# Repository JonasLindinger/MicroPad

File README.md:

# MicroPad — Wi-Fi MQTT Controller for Home Assistant

> AI-assisted development — firmware, HA automation, config generator and docs were created with AI (LLM) help, reviewed and tested by the author. Provided as-is, without warranty; verify on your own hardware, don't use for safety-critical applications.

MicroPad is a small ESP32-S3 desk controller with a 2.9" e-paper display, a 3×4
key matrix, and a rotary encoder. It talks to Home Assistant over MQTT and shows
clickable pages of your devices, media, scripts, scenes, and numbers. This
repository contains the firmware, the Home Assistant automation generator, the
web configurator, and the deployment/service assets.

## Safety

- **Not safety-critical.** This project is a convenience input device. Do not use
  it, or rely on it, for safety-critical applications (life-safety, medical,
  security, or anything where a missed or delayed press could cause harm). The
  room always retains the Home Assistant UI as the authoritative control surface.
- **Verify on your own hardware.** Firmware behaviour is validated by the compile
  matrix and host/static suites on this build machine, but no physical MicroPad
  hardware was available during development. Every hardware acceptance row is
  intentionally unchecked until an operator executes it on real hardware. Never
  assume a feature works on your specific board; test it.
- **Neutral placeholders only.** Source contains no real credentials. The broker
  host placeholder is `192.168.0.100`, the service user is `micropad`, and the
  placeholder password is `replace-me`. Real Wi-Fi/MQTT credentials are entered
  only through the on-device setup portal and stored in NVS.
- **Charge-only chargers.** A charge-only wall charger (no enumerated USB host)
  intentionally follows normal battery sleep behaviour: no power icon is drawn
  and light sleep is allowed. Only an enumerated USB data host keeps the device
  fully awake. See `docs/hardware-acceptance.md`.

## Reproducibility

The Python dependency graph is locked: `uv.lock` is the resolved source of
truth, and `requirements-lock.txt` is its content-hash materialization (every
wheel pinned with `sha256`, regenerated with `uv export --frozen`). The build
backend is pinned exactly (`setuptools==84.0.0`). This freezes dependency
*versions and content*; it does **not** claim byte-identical builds, because
pip/setuptools release artifacts can still vary between environments. Generated
automation/payload artifacts are deterministic per configuration (see below).

## Quick start

Create a virtualenv and install the package and dev tools (Ubuntu/Debian shown):

```bash
python3 -m venv .venv
.venv/bin/pip install --requirement requirements-dev.txt
```

For a content-hash-pinned runtime install (every transitive dependency locked in
`uv.lock` and materialized as `requirements-lock.txt` with `sha256` hashes)
instead use:

```bash
.venv/bin/pip install --requirement requirements-lock.txt
```

Run the configurator locally for development (Flask dev server):

```bash
.venv/bin/python -m flask --app micropad.wsgi:app run --host 127.0.0.1 --port 8080
```

Check it is healthy:

```bash
curl http://127.0.0.1:8080/healthz
# -> {"ok": true, "service": "micropad-configurator"}
```

For production, install the systemd service under `/opt/micropad/app` (root):

```bash
sudo ./scripts/setup.sh --enable-service
journalctl -u micropad.service -f
```

The on-device network setup and the build/flash workflow are described in
`docs/firmware.md`.

## Firmware

The firmware lives in `firmware/` (`MicroPad_HA_Controller.ino`,
`micropad_core.*`, and `protocol_contract.h`). It is built with Arduino CLI 1.5.1,
ESP32 core 3.3.11, GxEPD2 1.6.9, ArduinoJson 7.4.3, and PubSubClient 2.8.

```bash
./scripts/install-arduino-toolchain.sh        # pin the exact toolchain
./scripts/compile-firmware.sh --print-matrix  # list the three pinned FQBNs
./scripts/compile-firmware.sh                 # compile all matrix FQBNs
```

See `docs/firmware.md` for the pin map, build/flash commands, the setup portal,
and sleep behaviour.

## Home Assistant

A single MQTT automation (id `micropad_controller`) turns `micropad/event` and
`micropad/power` publications into device actions and re-publishes the
authoritative `micropad/pages/all`, `micropad/page/current`, and `micropad/keymap`
retained payloads. The automation and the retained initial payloads are generated
by `src/micropad/generator.py` and are byte-identical for the same configuration.

You can deliver the generated automation two ways:

- **API upload** — the configurator writes the automation directly to Home
  Assistant via its REST API and verifies the read-back, then publishes the
  retained MQTT payloads.
- **SSH upload** — the configurator uploads a YAML file to your Home Assistant
  host over SFTP/SSH with strict host-key checking and reloads, for setups where
  the REST API path is not available.

Both are covered in `docs/home-assistant.md`.

## Configurator

The Flask web configurator (`src/micropad/app.py`) validates your configuration,
lets you edit pages, key maps, and entity bindings in the browser, discovers
Home Assistant entities, and generates or uploads the automation.

- `GET /api/config` — current public configuration (credentials redacted).
- `POST /api/config` — validate and save a configuration.
- `POST /api/validate` — validate without saving.
- `POST /api/upload/api` — deploy via the Home Assistant REST API.
- `POST /api/upload/ssh` — deploy via SFTP/SSH.
- `GET /api/meta` — contract version, the fourteen key IDs, actions, item types,
  templates, and the default keymap.

See `docs/configurator.md` for the pages editor, key editor, entity discovery,
and validation rules, and `docs/deployment.md` for install/update/logs/uninstall.

---

Licensed under the [MIT License](LICENSE) (Copyright (c) 2026 Jonas Lindinger).
All content above is written in neutral English and uses only the placeholder
values described in the **Safety** section.

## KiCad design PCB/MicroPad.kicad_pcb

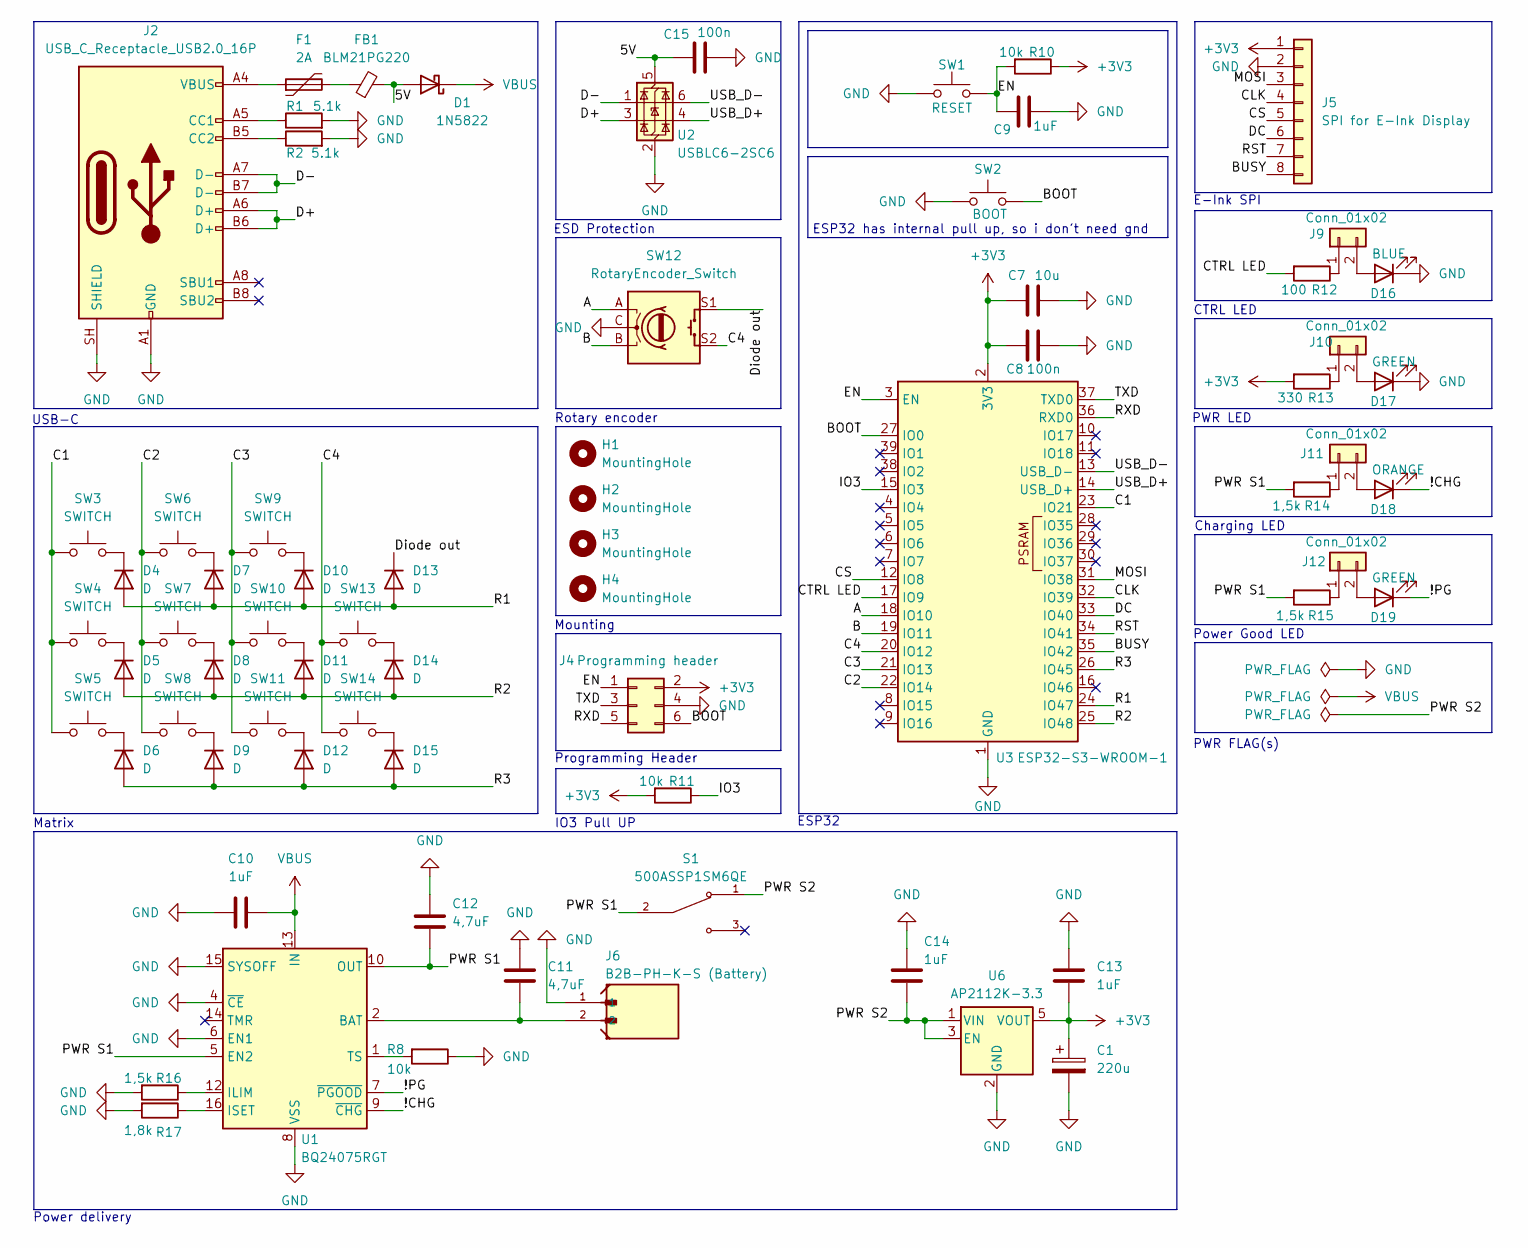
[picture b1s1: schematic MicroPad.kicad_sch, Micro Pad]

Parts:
C1: 220u; CP_Elec_6.3x7.7
C7: 10u; C_0805_2012Metric_Pad1.18x1.45mm_HandSolder
C8, C15: 100n; C_0805_2012Metric_Pad1.18x1.45mm_HandSolder
C9, C10, C13, C14: 1uF; C_0805_2012Metric_Pad1.18x1.45mm_HandSolder
C11, C12: 4,7uF; C_0805_2012Metric_Pad1.18x1.45mm_HandSolder
D1: 1N5822; D_DO-201AD_P15.24mm_Horizontal
D4, D5, D6, D7, D8, D9, D10, D11, D12, D13, D14, D15: D; D_SMA
D16: BLUE; LED_D3.0mm
D17, D19: GREEN; LED_D3.0mm
D18: ORANGE; LED_D3.0mm
F1: 2A; Fuse_0805_2012Metric_Pad1.15x1.40mm_HandSolder
FB1: BLM21PG220; L_0805_2012Metric_Pad1.05x1.20mm_HandSolder
H1, H2, H3, H4: MountingHole; MountingHole_3.2mm_M3_DIN965
J2: USB_C_Receptacle_USB2.0_16P; USB_C_Receptacle_GCT_USB4085
J4: Programming header; PinHeader_2x03_P2.54mm_Vertical
J5: SPI for E-Ink Display; PinHeader_1x08_P2.54mm_Vertical
J6: B2B-PH-K-S (Battery); JST_B2B-PH-K-S
J9, J10, J11, J12: Conn_01x02; SolderJumper-2_P1.3mm_Open_TrianglePad1.0x1.5mm
R1, R2: 5.1k; R_0805_2012Metric_Pad1.20x1.40mm_HandSolder
R8, R10, R11: 10k; R_0805_2012Metric_Pad1.20x1.40mm_HandSolder
R12: 100; R_0805_2012Metric_Pad1.20x1.40mm_HandSolder
R13: 330; R_0805_2012Metric_Pad1.20x1.40mm_HandSolder
R14, R15, R16: 1,5k; R_0805_2012Metric_Pad1.20x1.40mm_HandSolder
R17: 1,8k; R_0805_2012Metric_Pad1.20x1.40mm_HandSolder
S1: 500ASSP1SM6QE; SW_500ASSP1SM6QE; PARTREV A
SW1: RESET; SW_PUSH_6mm
SW2: BOOT; SW_PUSH_6mm
SW3, SW4, SW5, SW6, SW7, SW8, SW9, SW10, SW11, SW13, SW14: SWITCH; SW_Cherry_MX_1.00u_PCB
SW12: RotaryEncoder_Switch; RotaryEncoder_Alps_EC11E-Switch_Vertical_H20mm
U1: BQ24075RGT; VQFN-16-1EP_3x3mm_P0.5mm_EP1.6x1.6mm
U2: USBLC6-2SC6; SOT-23-6
U3: ESP32-S3-WROOM-1
U6: AP2112K-3.3; SOT-23-5

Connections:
+3V3: C1.1, C7.1, C8.1, C13.2, J4.2, J5.1, R10.1, R11.2, R13.2, U3.2 (3V3), U6.5 (VOUT)
/5V: C15.1, D1.2 (A), FB1.2, U2.5 (VBUS)
/!CHG: D18.1 (K), U1.9 (~CHG)
/!PG: D19.1 (K), U1.7 (~PGOOD)
/A: SW12.A, U3.18 (IO10)
/B: SW12.B, U3.19 (IO11)
/BOOT: J4.6, SW2.2, U3.27 (IO0)
/BUSY: J5.8, U3.35 (IO42)
/C1: SW3.1, SW4.1, SW5.1, U3.23 (IO21)
/C2: SW6.1, SW7.1, SW8.1, U3.22 (IO14)
/C3: SW9.1, SW10.1, SW11.1, U3.21 (IO13)
/C4: SW12.S2, SW13.1, SW14.1, U3.20 (IO12)
/CLK: J5.4, U3.32 (IO39)
/CS: J5.5, U3.12 (IO8)
/CTRL LED: R12.2, U3.17 (IO9)
/D+: J2.A6 (D+), J2.B6 (D+), U2.3 (I/O2)
/D-: J2.A7 (D-), J2.B7 (D-), U2.1 (I/O1)
/DC: J5.6, U3.33 (IO40)
/Diode out: D13.1 (K), SW12.S1
/EN: C9.1, J4.1, R10.2, SW1.2, U3.3 (EN)
/IO3: R11.1, U3.15 (IO3)
/MOSI: J5.3, U3.31 (IO38)
/PWR S1: C12.2, R14.2, R15.2, S1.2, U1.5 (EN2), U1.10 (OUT), U1.11 (OUT)
/PWR S2: C14.2, S1.1, U6.1 (VIN), U6.3 (EN)
/R1: D4.2 (A), D7.2 (A), D10.2 (A), D13.2 (A), U3.24 (IO47)
/R2: D5.2 (A), D8.2 (A), D11.2 (A), D14.2 (A), U3.25 (IO48)
/R3: D6.2 (A), D9.2 (A), D12.2 (A), D15.2 (A), U3.26 (IO45)
/RST: J5.7, U3.34 (IO41)
/RXD: J4.5, U3.36 (RXD0)
/TXD: J4.3, U3.37 (TXD0)
/USB_D+: U2.4 (I/O2), U3.14 (USB_D+)
/USB_D-: U2.6 (I/O1), U3.13 (USB_D-)
GND: C1.2, C7.2, C8.2, C9.2, C10.2, C11.1, C12.1, C13.1, C14.1, C15.2, D16.1 (K), D17.1 (K), J2.A1 (GND), J2.A12 (GND), J2.B1 (GND), J2.B12 (GND), J2.SH (SHIELD), J4.4, J5.2, J6.1, R1.2, R2.2, R8.1, R16.2, R17.2, SW1.1, SW2.1, SW12.C, U1.4 (~CE), U1.6 (EN1), U1.8 (VSS), U1.15 (SYSOFF), U1.17 (VSS), U2.2 (GND), U3.1 (GND), U3.40 (GND), U3.41 (GND), U6.2 (GND)
unnamed: C11.2, J6.2, U1.2 (BAT), U1.3 (BAT)
unnamed: D4.1 (K), SW3.2
unnamed: D5.1 (K), SW4.2
unnamed: D6.1 (K), SW5.2
unnamed: D7.1 (K), SW6.2
unnamed: D8.1 (K), SW7.2
unnamed: D9.1 (K), SW8.2
unnamed: D10.1 (K), SW9.2
unnamed: D11.1 (K), SW10.2
unnamed: D12.1 (K), SW11.2
unnamed: D14.1 (K), SW13.2
unnamed: D15.1 (K), SW14.2
unnamed: D16.2 (A), J9.2
unnamed: D17.2 (A), J10.2
unnamed: D18.2 (A), J11.2
unnamed: D19.2 (A), J12.2
unnamed: F1.1, J2.A4 (VBUS), J2.A9 (VBUS), J2.B4 (VBUS), J2.B9 (VBUS)
unnamed: F1.2, FB1.1
unnamed: J2.A5 (CC1), R1.1
unnamed: J2.B5 (CC2), R2.1
unnamed: J9.1, R12.1
unnamed: J10.1, R13.1
unnamed: J11.1, R14.1
unnamed: J12.1, R15.1
unnamed: R16.1, U1.12 (ILIM)
unnamed: R17.1, U1.16 (ISET)
unnamed: R8.2, U1.1 (TS)
VBUS: C10.1, D1.1 (K), U1.13 (IN)

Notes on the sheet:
CTRL LED
PWR FLAG(s)
PWR LED
ESP32
E-Ink SPI
IO3 Pull UP
Programming Header
Matrix
ESD Protection
Power delivery
Rotary encoder
Power Good LED
Mounting
Charging LED
ESP32 has internal pull up, so i don't need gnd
USB-C

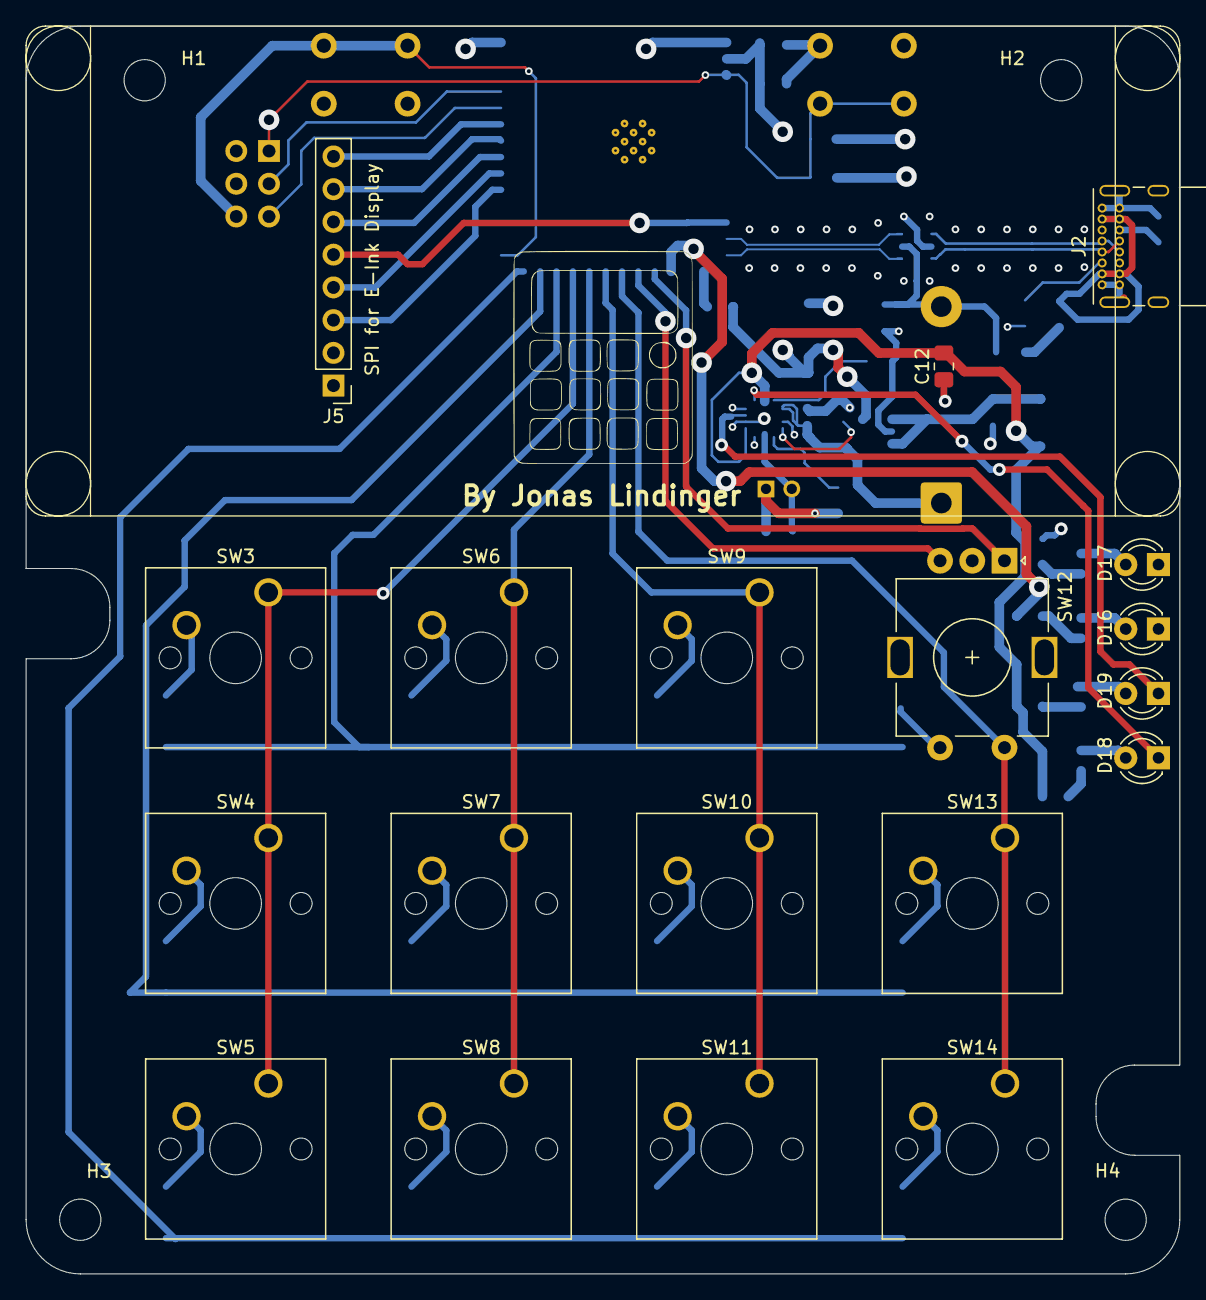
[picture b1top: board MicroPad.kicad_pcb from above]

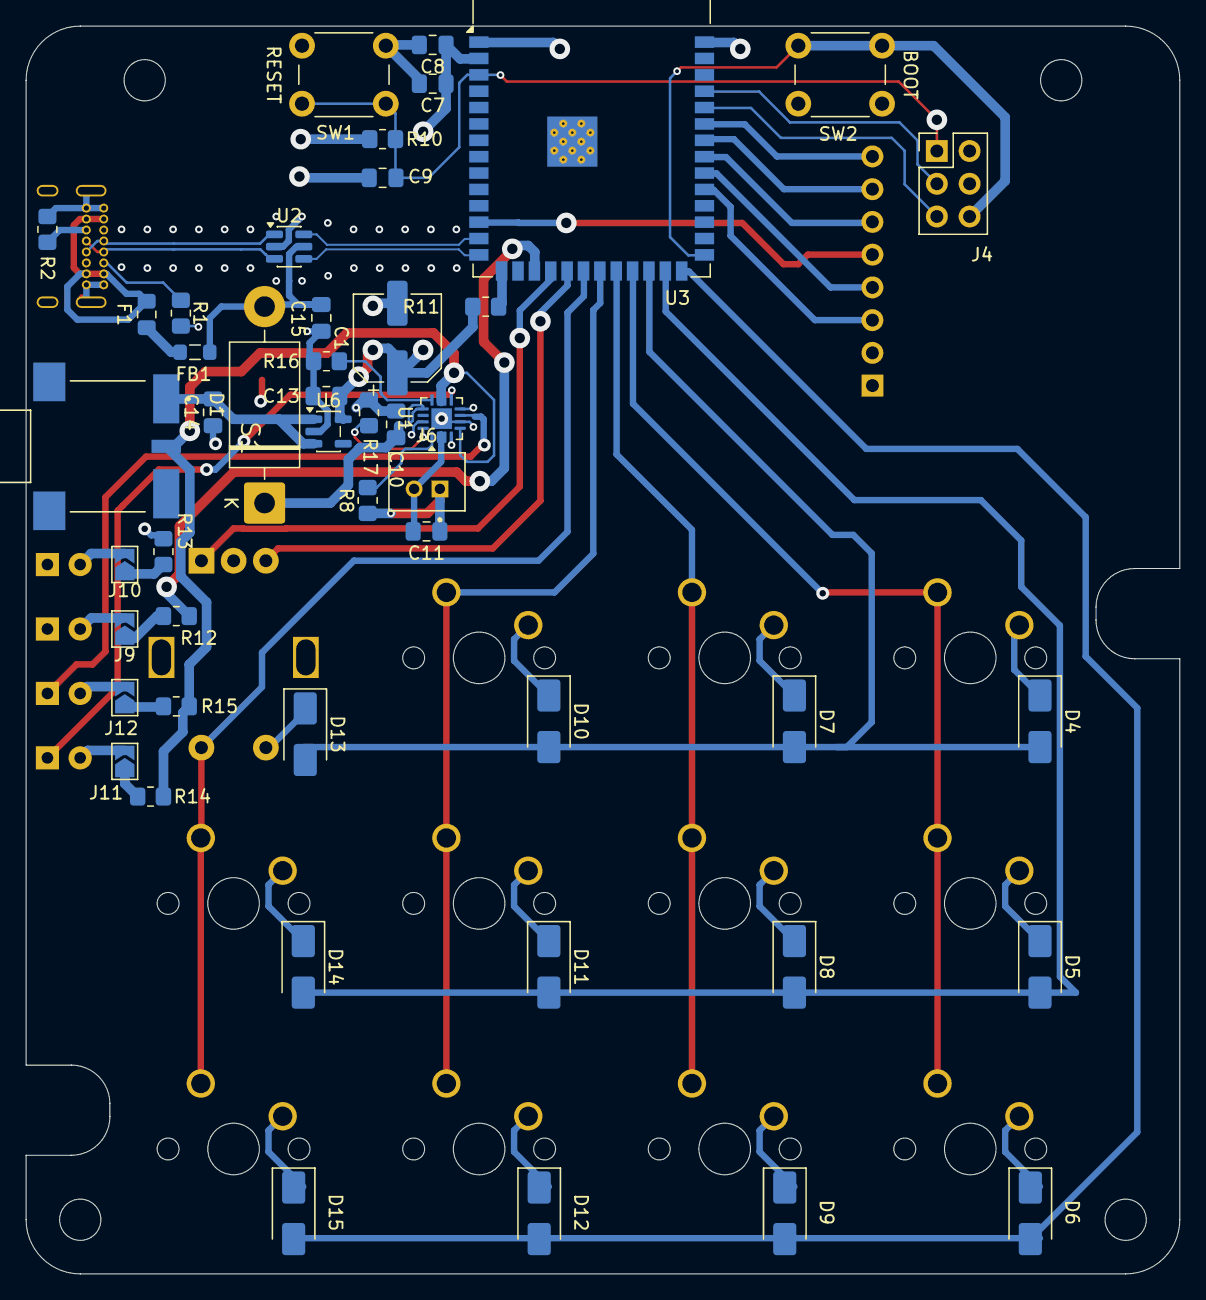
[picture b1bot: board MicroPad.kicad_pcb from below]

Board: 4 copper layers, 89.5 x 96.8 mm, 71 parts (48 on the bottom side), 61 nets.

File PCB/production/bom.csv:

Designator,Footprint,Quantity,Value,LCSC Part #
C1,CP_Elec_6.3x7.7,1,220u,
"C10, C13, C14, C9",0805,4,1uF,
"C11, C12",0805,2,"4,7uF",
"C15, C8",0805,2,100n,
C7,0805,1,10u,
D1,D_DO-201AD_P15.24mm_Horizontal,1,1N5822,
"D10, D11, D12, D13, D14, D15, D4, D5, D6, D7, D8, D9",D_SMA,12,D,
D16,LED_D3.0mm,1,BLUE,
"D17, D19",LED_D3.0mm,2,GREEN,
D18,LED_D3.0mm,1,ORANGE,
F1,0805,1,2A,
FB1,0805,1,BLM21PG220,
"J10, J11, J12, J9",SolderJumper-2_P1.3mm_Open_TrianglePad1.0x1.5mm,4,Conn_01x02,
J2,USB_C_Receptacle_GCT_USB4085,1,USB_C_Receptacle_USB2.0_16P,
J4,PinHeader_2x03_P2.54mm_Vertical,1,Programming header,
J5,PinHeader_1x08_P2.54mm_Vertical,1,SPI for E-Ink Display,
J6,JST_B2B-PH-K-S,1,B2B-PH-K-S (Battery),
"R1, R2",0805,2,5.1k,
"R10, R11, R8",0805,3,10k,
R12,0805,1,100,
R13,0805,1,330,
"R14, R15, R16",0805,3,"1,5k",
R17,0805,1,"1,8k",
S1,SW_500ASSP1SM6QE,1,500ASSP1SM6QE,
SW1,SW_PUSH_6mm,1,RESET,
"SW10, SW11, SW13, SW14, SW3, SW4, SW5, SW6, SW7, SW8, SW9",SW_Cherry_MX_1.00u_PCB,11,SWITCH,
SW12,RotaryEncoder_Alps_EC11E-Switch_Vertical_H20mm,1,RotaryEncoder_Switch,
SW2,SW_PUSH_6mm,1,BOOT,
U1,VQFN-16-1EP_3x3mm_P0.5mm_EP1.6x1.6mm,1,BQ24075RGT,
U2,SOT-23-6,1,USBLC6-2SC6,
U3,ESP32-S3-WROOM-1,1,ESP32-S3-WROOM-1,
U6,SOT-23-5,1,AP2112K-3.3,
